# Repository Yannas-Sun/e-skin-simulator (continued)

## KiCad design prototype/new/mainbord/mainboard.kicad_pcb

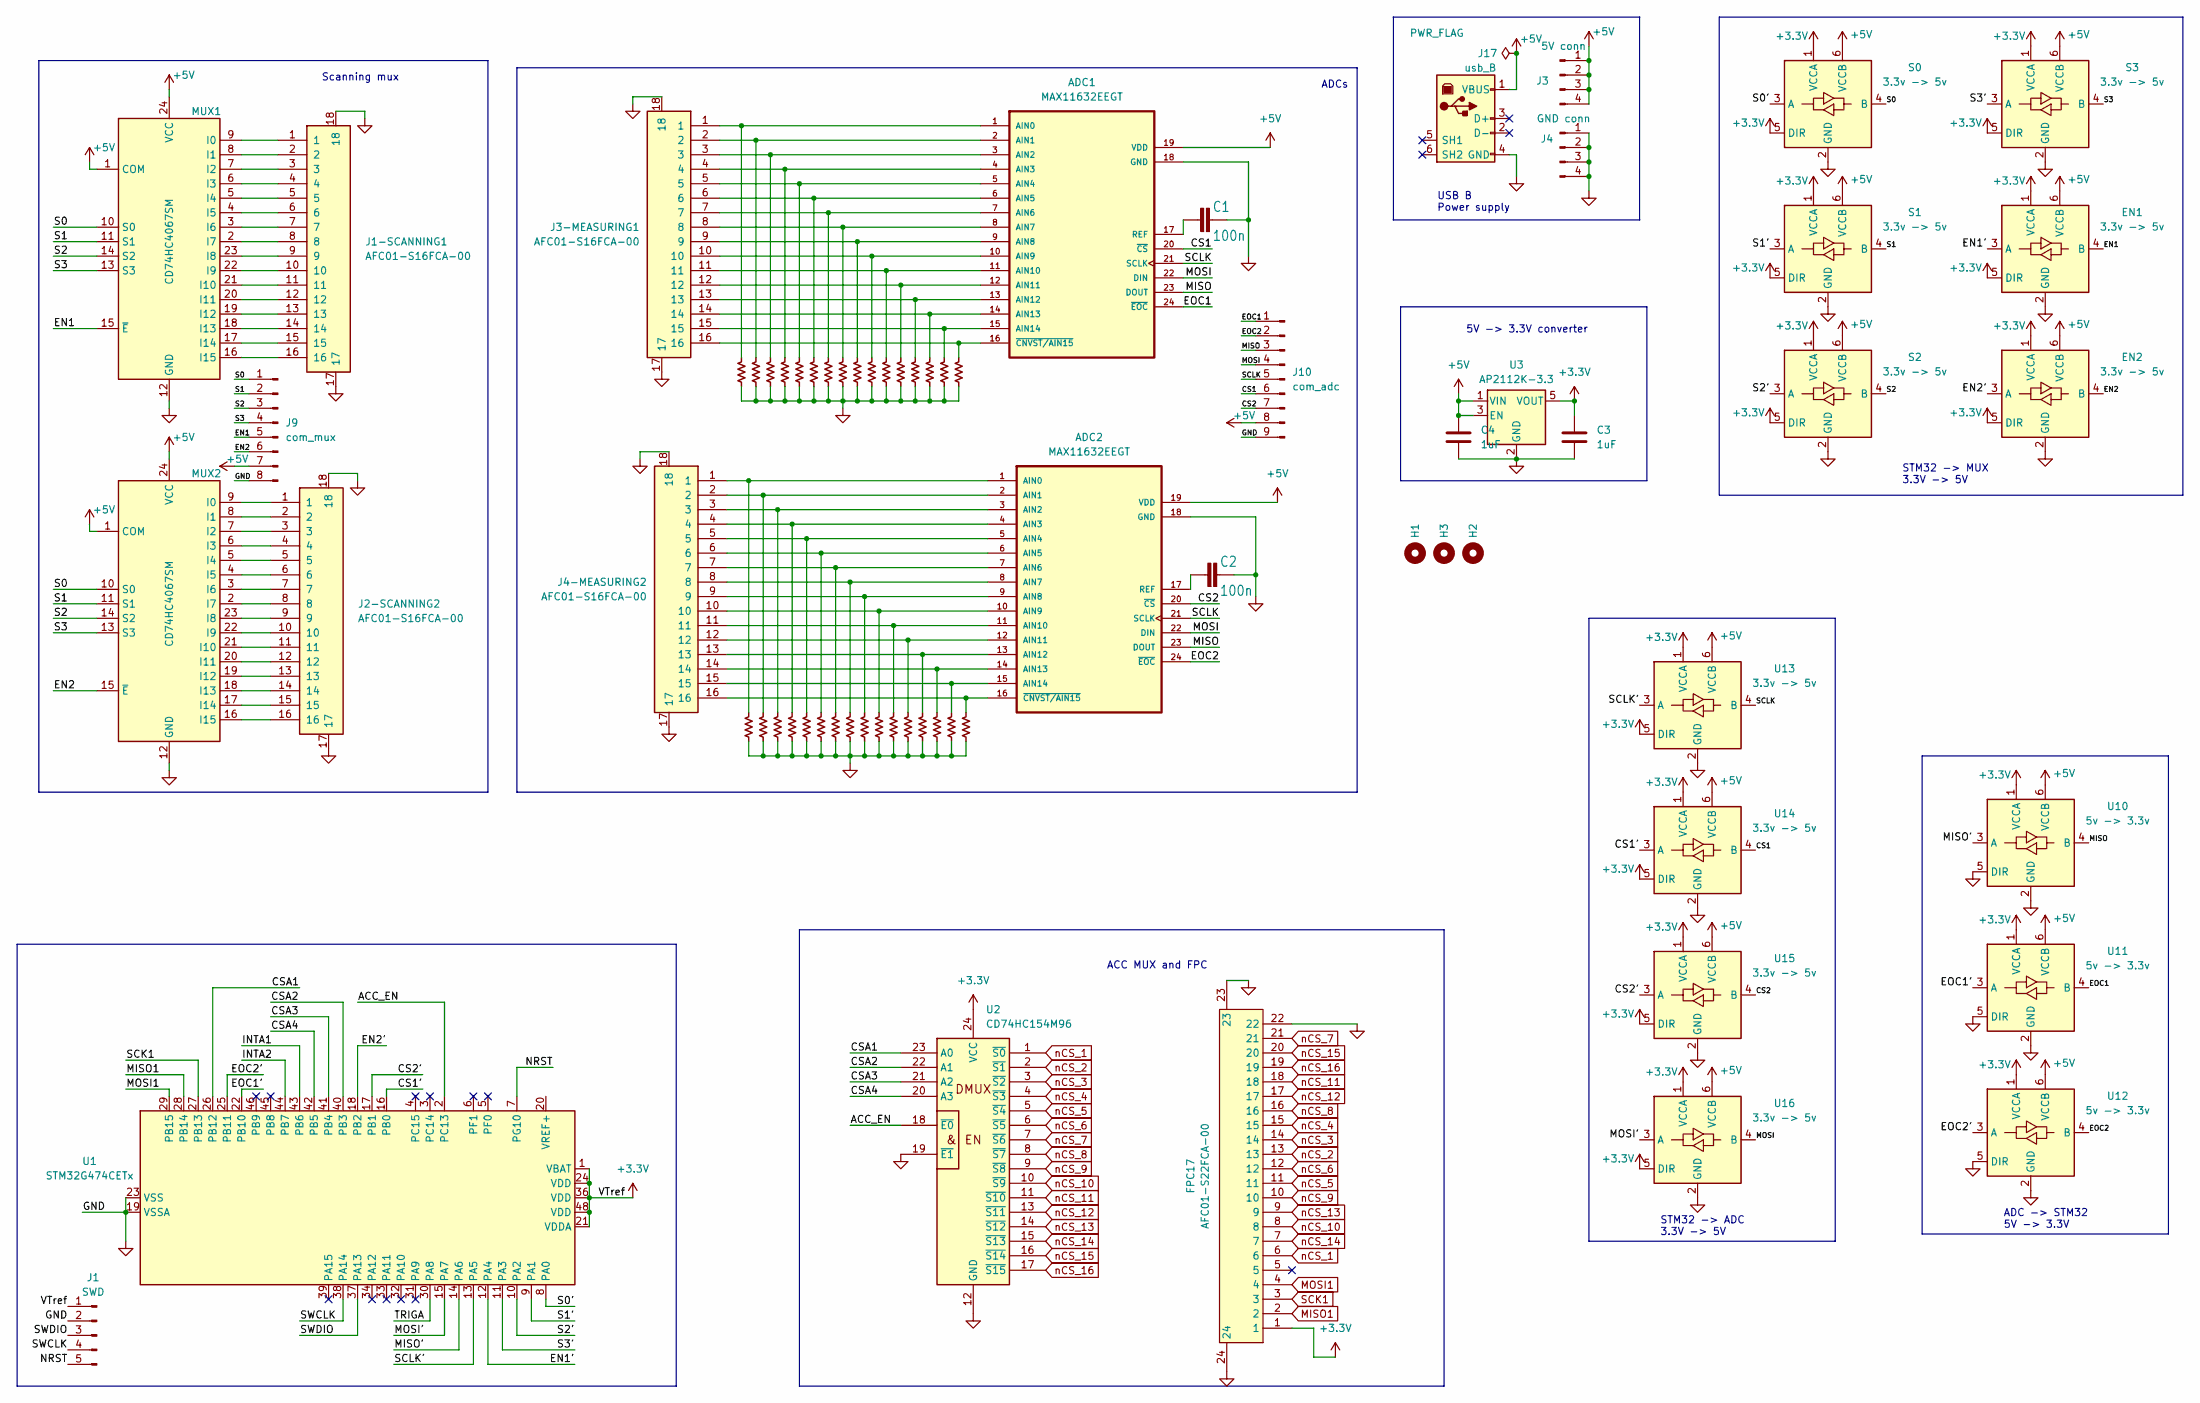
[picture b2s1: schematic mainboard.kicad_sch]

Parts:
ADC1, ADC2: MAX11632EEGT
C1, C2: 100n; C0603
C3, C4: 1uF; C0603
EN1, EN2: 3.3v -> 5v; SOT-363_SC-70-6
FPC17: AFC01-S22FCA-00; LCSC Part C262668
H1, H2, H3: MountingHole; MountingHole_3.2mm_M3
J1: SWD; PinHeader_1x05_P2.54mm_Vertical
J1-SCANNING1, J2-SCANNING2, J3-MEASURING1, J4-MEASURING2: AFC01-S16FCA-00
J3: 5V conn; PinHeader_1x04_P2.54mm_Horizontal
J4: GND conn; PinHeader_1x04_P2.54mm_Horizontal
J9: com_mux; PinHeader_1x08_P2.54mm_Vertical
J10: com_adc; PinHeader_1x09_P2.54mm_Vertical
J17: usb_B; SS52300001; Mouser Part Number 530-SS-52300-001
MUX1, MUX2: CD74HC4067SM; SSOP-24_5.3x8.2mm_P0.65mm
S0, S1, S2, S3: 3.3v -> 5v; SOT-363_SC-70-6
U1: STM32G474CETx; LQFP-48_7x7mm_P0.5mm
U2: CD74HC154M96; SOIC127P1030X265-24N
U3: AP2112K-3.3; SOT-23-5
U10, U11, U12: 5v -> 3.3v; SOT-363_SC-70-6
U13, U14, U15, U16: 3.3v -> 5v; SOT-363_SC-70-6
U$2, U$4, U$6, U$8, U$10, U$12, U$14, U$16, U$18, U$20, U$22, U$24, U$26, U$28, U$30, U$32, U$34, U$36, U$38, U$40, U$42, U$44, U$46, U$48, U$50, U$52, U$54, U$56, U$58, U$60, U$62, U$64: 10k; R_0603_1608Metric

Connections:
+3.3V: C3.1, EN1.1 (VCCA), EN1.5 (DIR), EN2.1 (VCCA), EN2.5 (DIR), FPC17.1, J1.1, S0.1 (VCCA), S0.5 (DIR), S1.1 (VCCA), S1.5 (DIR), S2.1 (VCCA), S2.5 (DIR), S3.1 (VCCA), S3.5 (DIR), U1.1 (VBAT), U1.21 (VDDA), U1.24 (VDD), U1.36 (VDD), U1.48 (VDD), U2.24 (VCC), U3.5 (VOUT), U10.1 (VCCA), U11.1 (VCCA), U12.1 (VCCA), U13.1 (VCCA), U13.5 (DIR), U14.1 (VCCA), U14.5 (DIR), U15.1 (VCCA), U15.5 (DIR), U16.1 (VCCA), U16.5 (DIR)
+5V: ADC1.19 (VDD), ADC2.19 (VDD), C4.1, EN1.6 (VCCB), EN2.6 (VCCB), J3.1, J3.2, J3.3, J3.4, J9.7, J10.8, J17.1 (VBUS), MUX1.1 (COM), MUX1.24 (VCC), MUX2.1 (COM), MUX2.24 (VCC), S0.6 (VCCB), S1.6 (VCCB), S2.6 (VCCB), S3.6 (VCCB), U3.1 (VIN), U3.3 (EN), U10.6 (VCCB), U11.6 (VCCB), U12.6 (VCCB), U13.6 (VCCB), U14.6 (VCCB), U15.6 (VCCB), U16.6 (VCCB)
/ACC_EN: U1.2 (PC13), U2.18 (~E0)
/CS1: ADC1.20 (~CS), J10.6, U14.4 (B)
/CS1': U1.16 (PB0), U14.3 (A)
/CS2: ADC2.20 (~CS), J10.7, U15.4 (B)
/CS2': U1.17 (PB1), U15.3 (A)
/CSA1: U1.26 (PB12), U2.23 (A0)
/CSA2: U1.40 (PB3), U2.22 (A1)
/CSA3: U1.41 (PB4), U2.21 (A2)
/CSA4: U1.42 (PB5), U2.20 (A3)
/EN1: EN1.4 (B), J9.5, MUX1.15 (~E)
/EN1': EN1.3 (A), U1.12 (PA4)
/EN2: EN2.4 (B), J9.6, MUX2.15 (~E)
/EN2': EN2.3 (A), U1.18 (PB2)
/EOC1: ADC1.24 (~EOC), J10.1, U11.4 (B)
/EOC1': U1.22 (PB10), U11.3 (A)
/EOC2: ADC2.24 (~EOC), J10.2, U12.4 (B)
/EOC2': U1.25 (PB11), U12.3 (A)
/INTA1: U1.43 (PB6)
/INTA2: U1.44 (PB7)
/MISO: ADC1.23 (DOUT), ADC2.23 (DOUT), J10.3, U10.4 (B)
/MISO': U1.14 (PA6), U10.3 (A)
/MOSI: ADC1.22 (DIN), ADC2.22 (DIN), J10.4, U16.4 (B)
/MOSI': U1.15 (PA7), U16.3 (A)
/NRST: J1.5, U1.7 (PG10)
/S0: J9.1, MUX1.10 (S0), MUX2.10 (S0), S0.4 (B)
/S0': S0.3 (A), U1.8 (PA0)
/S1: J9.2, MUX1.11 (S1), MUX2.11 (S1), S1.4 (B)
/S1': S1.3 (A), U1.9 (PA1)
/S2: J9.3, MUX1.14 (S2), MUX2.14 (S2), S2.4 (B)
/S2': S2.3 (A), U1.10 (PA2)
/S3: J9.4, MUX1.13 (S3), MUX2.13 (S3), S3.4 (B)
/S3': S3.3 (A), U1.11 (PA3)
/SCLK: ADC1.21 (SCLK), ADC2.21 (SCLK), J10.5, U13.4 (B)
/SCLK': U1.13 (PA5), U13.3 (A)
/SWCLK: J1.4, U1.38 (PA14)
/SWDIO: J1.3, U1.37 (PA13)
/TRIGA: U1.30 (PA8)
GND: ADC1.18 (GND), ADC2.18 (GND), C1.2, C2.2, C3.2, C4.2, EN1.2 (GND), EN2.2 (GND), FPC17.22, FPC17.23, FPC17.24, J1.2, J1-SCANNING1.17, J1-SCANNING1.18, J2-SCANNING2.17, J2-SCANNING2.18, J3-MEASURING1.17, J3-MEASURING1.18, J4.1, J4.2, J4.3, J4.4, J4-MEASURING2.17, J4-MEASURING2.18, J9.8, J10.9, J17.4 (GND), MUX1.12 (GND), MUX2.12 (GND), S0.2 (GND), S1.2 (GND), S2.2 (GND), S3.2 (GND), U1.19 (VSSA), U1.23 (VSS), U1.35 (VSS), U1.47 (VSS), U2.12 (GND), U2.19 (~E1), U3.2 (GND), U10.2 (GND), U10.5 (DIR), U11.2 (GND), U11.5 (DIR), U12.2 (GND), U12.5 (DIR), U13.2 (GND), U14.2 (GND), U15.2 (GND), U16.2 (GND), U$2.2, U$4.2, U$6.2, U$8.2, U$10.2, U$12.2, U$14.2, U$16.2, U$18.2, U$20.2, U$22.2, U$24.2, U$26.2, U$28.2, U$30.2, U$32.2, U$34.2, U$36.2, U$38.2, U$40.2, U$42.2, U$44.2, U$46.2, U$48.2, U$50.2, U$52.2, U$54.2, U$56.2, U$58.2, U$60.2, U$62.2, U$64.2
MISO1: FPC17.2, U1.28 (PB14)
MOSI1: FPC17.4, U1.29 (PB15)
unnamed: ADC1.1 (AIN0), J3-MEASURING1.1, U$16.1
unnamed: ADC1.2 (AIN1), J3-MEASURING1.2, U$14.1
unnamed: ADC1.3 (AIN2), J3-MEASURING1.3, U$12.1
unnamed: ADC1.4 (AIN3), J3-MEASURING1.4, U$10.1
unnamed: ADC1.5 (AIN4), J3-MEASURING1.5, U$8.1
unnamed: ADC1.6 (AIN5), J3-MEASURING1.6, U$6.1
unnamed: ADC1.7 (AIN6), J3-MEASURING1.7, U$4.1
unnamed: ADC1.8 (AIN7), J3-MEASURING1.8, U$2.1
unnamed: ADC1.9 (AIN8), J3-MEASURING1.9, U$32.1
unnamed: ADC1.10 (AIN9), J3-MEASURING1.10, U$30.1
unnamed: ADC1.11 (AIN10), J3-MEASURING1.11, U$28.1
unnamed: ADC1.12 (AIN11), J3-MEASURING1.12, U$26.1
unnamed: ADC1.13 (AIN12), J3-MEASURING1.13, U$24.1
unnamed: ADC1.14 (AIN13), J3-MEASURING1.14, U$22.1
unnamed: ADC1.15 (AIN14), J3-MEASURING1.15, U$20.1
unnamed: ADC1.17 (REF), C1.1
unnamed: ADC1.16 (~CNVST/AIN15), J3-MEASURING1.16, U$18.1
unnamed: ADC2.1 (AIN0), J4-MEASURING2.1, U$48.1
unnamed: ADC2.2 (AIN1), J4-MEASURING2.2, U$46.1
unnamed: ADC2.3 (AIN2), J4-MEASURING2.3, U$44.1
unnamed: ADC2.4 (AIN3), J4-MEASURING2.4, U$42.1
unnamed: ADC2.5 (AIN4), J4-MEASURING2.5, U$40.1
unnamed: ADC2.6 (AIN5), J4-MEASURING2.6, U$38.1
unnamed: ADC2.7 (AIN6), J4-MEASURING2.7, U$36.1
unnamed: ADC2.8 (AIN7), J4-MEASURING2.8, U$34.1
unnamed: ADC2.9 (AIN8), J4-MEASURING2.9, U$64.1
unnamed: ADC2.10 (AIN9), J4-MEASURING2.10, U$62.1
unnamed: ADC2.11 (AIN10), J4-MEASURING2.11, U$60.1
unnamed: ADC2.12 (AIN11), J4-MEASURING2.12, U$58.1
unnamed: ADC2.13 (AIN12), J4-MEASURING2.13, U$56.1
unnamed: ADC2.14 (AIN13), J4-MEASURING2.14, U$54.1
unnamed: ADC2.15 (AIN14), J4-MEASURING2.15, U$52.1
unnamed: ADC2.17 (REF), C2.1
unnamed: ADC2.16 (~CNVST/AIN15), J4-MEASURING2.16, U$50.1
unnamed: J1-SCANNING1.1, MUX1.9 (I0)
unnamed: J1-SCANNING1.2, MUX1.8 (I1)
unnamed: J1-SCANNING1.3, MUX1.7 (I2)
unnamed: J1-SCANNING1.4, MUX1.6 (I3)
unnamed: J1-SCANNING1.5, MUX1.5 (I4)
unnamed: J1-SCANNING1.6, MUX1.4 (I5)
unnamed: J1-SCANNING1.7, MUX1.3 (I6)
unnamed: J1-SCANNING1.8, MUX1.2 (I7)
unnamed: J1-SCANNING1.9, MUX1.23 (I8)
unnamed: J1-SCANNING1.10, MUX1.22 (I9)
unnamed: J1-SCANNING1.11, MUX1.21 (I10)
unnamed: J1-SCANNING1.12, MUX1.20 (I11)
unnamed: J1-SCANNING1.13, MUX1.19 (I12)
unnamed: J1-SCANNING1.14, MUX1.18 (I13)
unnamed: J1-SCANNING1.15, MUX1.17 (I14)
unnamed: J1-SCANNING1.16, MUX1.16 (I15)
unnamed: J2-SCANNING2.1, MUX2.9 (I0)
unnamed: J2-SCANNING2.2, MUX2.8 (I1)
unnamed: J2-SCANNING2.3, MUX2.7 (I2)
unnamed: J2-SCANNING2.4, MUX2.6 (I3)
unnamed: J2-SCANNING2.5, MUX2.5 (I4)
unnamed: J2-SCANNING2.6, MUX2.4 (I5)
unnamed: J2-SCANNING2.7, MUX2.3 (I6)
unnamed: J2-SCANNING2.8, MUX2.2 (I7)
unnamed: J2-SCANNING2.9, MUX2.23 (I8)
unnamed: J2-SCANNING2.10, MUX2.22 (I9)
unnamed: J2-SCANNING2.11, MUX2.21 (I10)
unnamed: J2-SCANNING2.12, MUX2.20 (I11)
unnamed: J2-SCANNING2.13, MUX2.19 (I12)
unnamed: J2-SCANNING2.14, MUX2.18 (I13)
unnamed: J2-SCANNING2.15, MUX2.17 (I14)
unnamed: J2-SCANNING2.16, MUX2.16 (I15)
SCK1: FPC17.3, U1.27 (PB13)
nCS_1: FPC17.6, U2.1 (~S0)
nCS_2: FPC17.13, U2.2 (~S1)
nCS_3: FPC17.14, U2.3 (~S2)
nCS_4: FPC17.15, U2.4 (~S3)
nCS_5: FPC17.11, U2.5 (~S4)
nCS_6: FPC17.12, U2.6 (~S5)
nCS_7: FPC17.21, U2.7 (~S6)
nCS_8: FPC17.16, U2.8 (~S7)
nCS_9: FPC17.10, U2.9 (~S8)
nCS_10: FPC17.8, U2.10 (~S9)
nCS_11: FPC17.18, U2.11 (~S10)
nCS_12: FPC17.17, U2.13 (~S11)
nCS_13: FPC17.9, U2.14 (~S12)
nCS_14: FPC17.7, U2.15 (~S13)
nCS_15: FPC17.20, U2.16 (~S14)
nCS_16: FPC17.19, U2.17 (~S15)

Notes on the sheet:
ADCs
USB B Power supply
ADC -> STM32 5V -> 3.3V
STM32 -> MUX 3.3V -> 5V
5V -> 3.3V converter
ACC MUX and FPC
Scanning mux
STM32 -> ADC 3.3V -> 5V

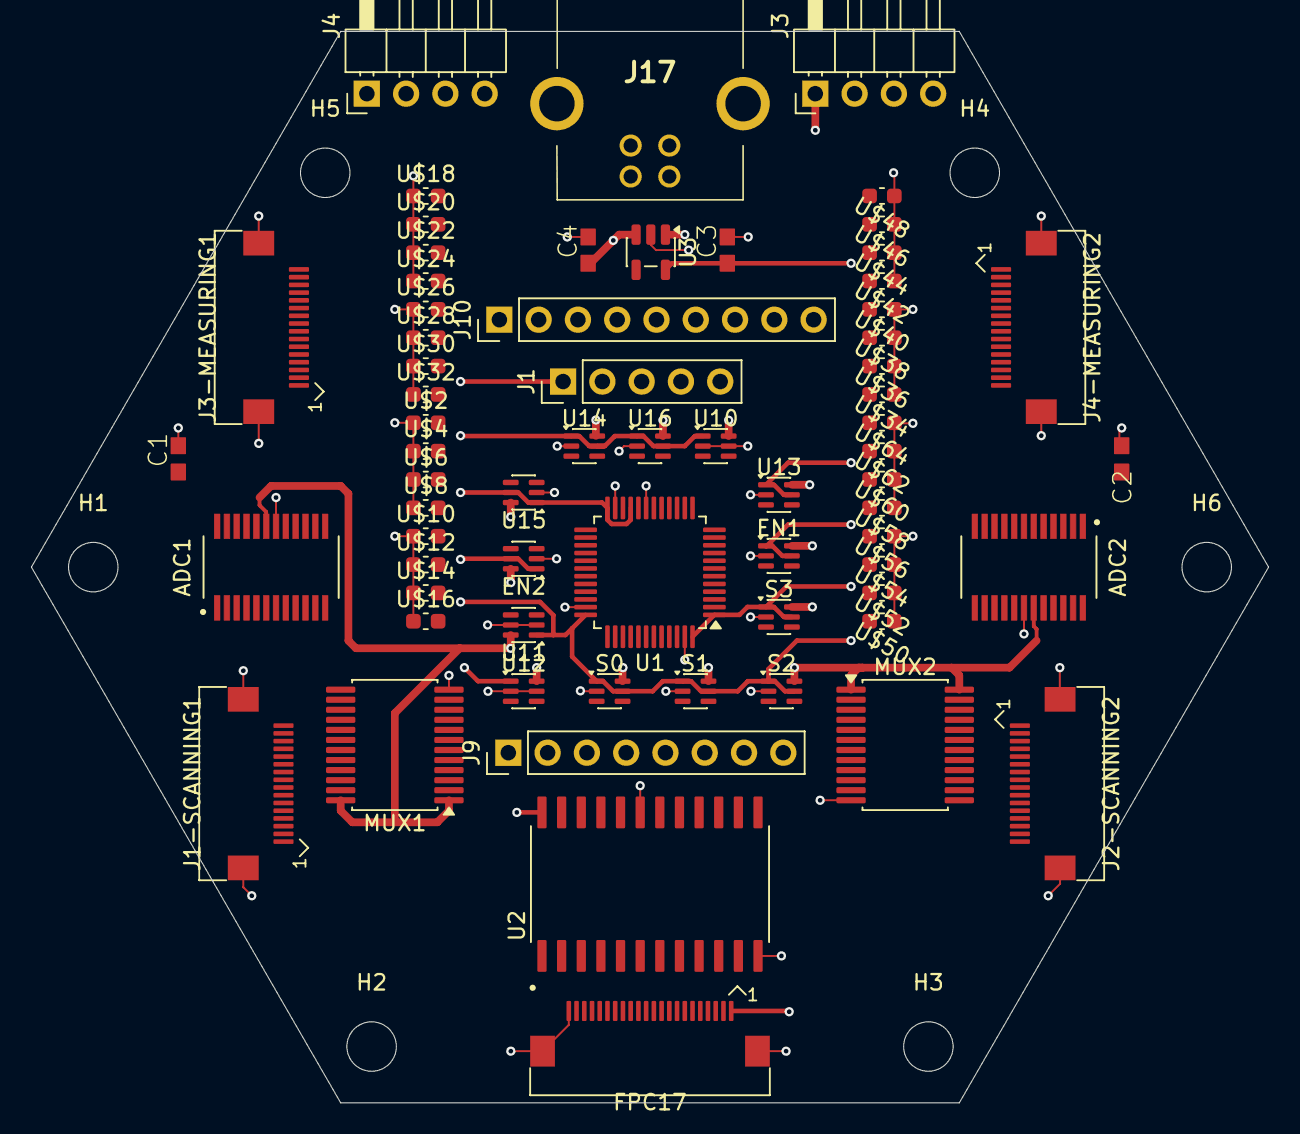
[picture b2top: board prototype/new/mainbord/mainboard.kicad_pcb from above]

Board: 4 copper layers, 80.0 x 69.3 mm, 73 parts (0 on the bottom side), 122 nets.

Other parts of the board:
H4, H5, H6: MountingHole; MountingHole_3.2mm_M3

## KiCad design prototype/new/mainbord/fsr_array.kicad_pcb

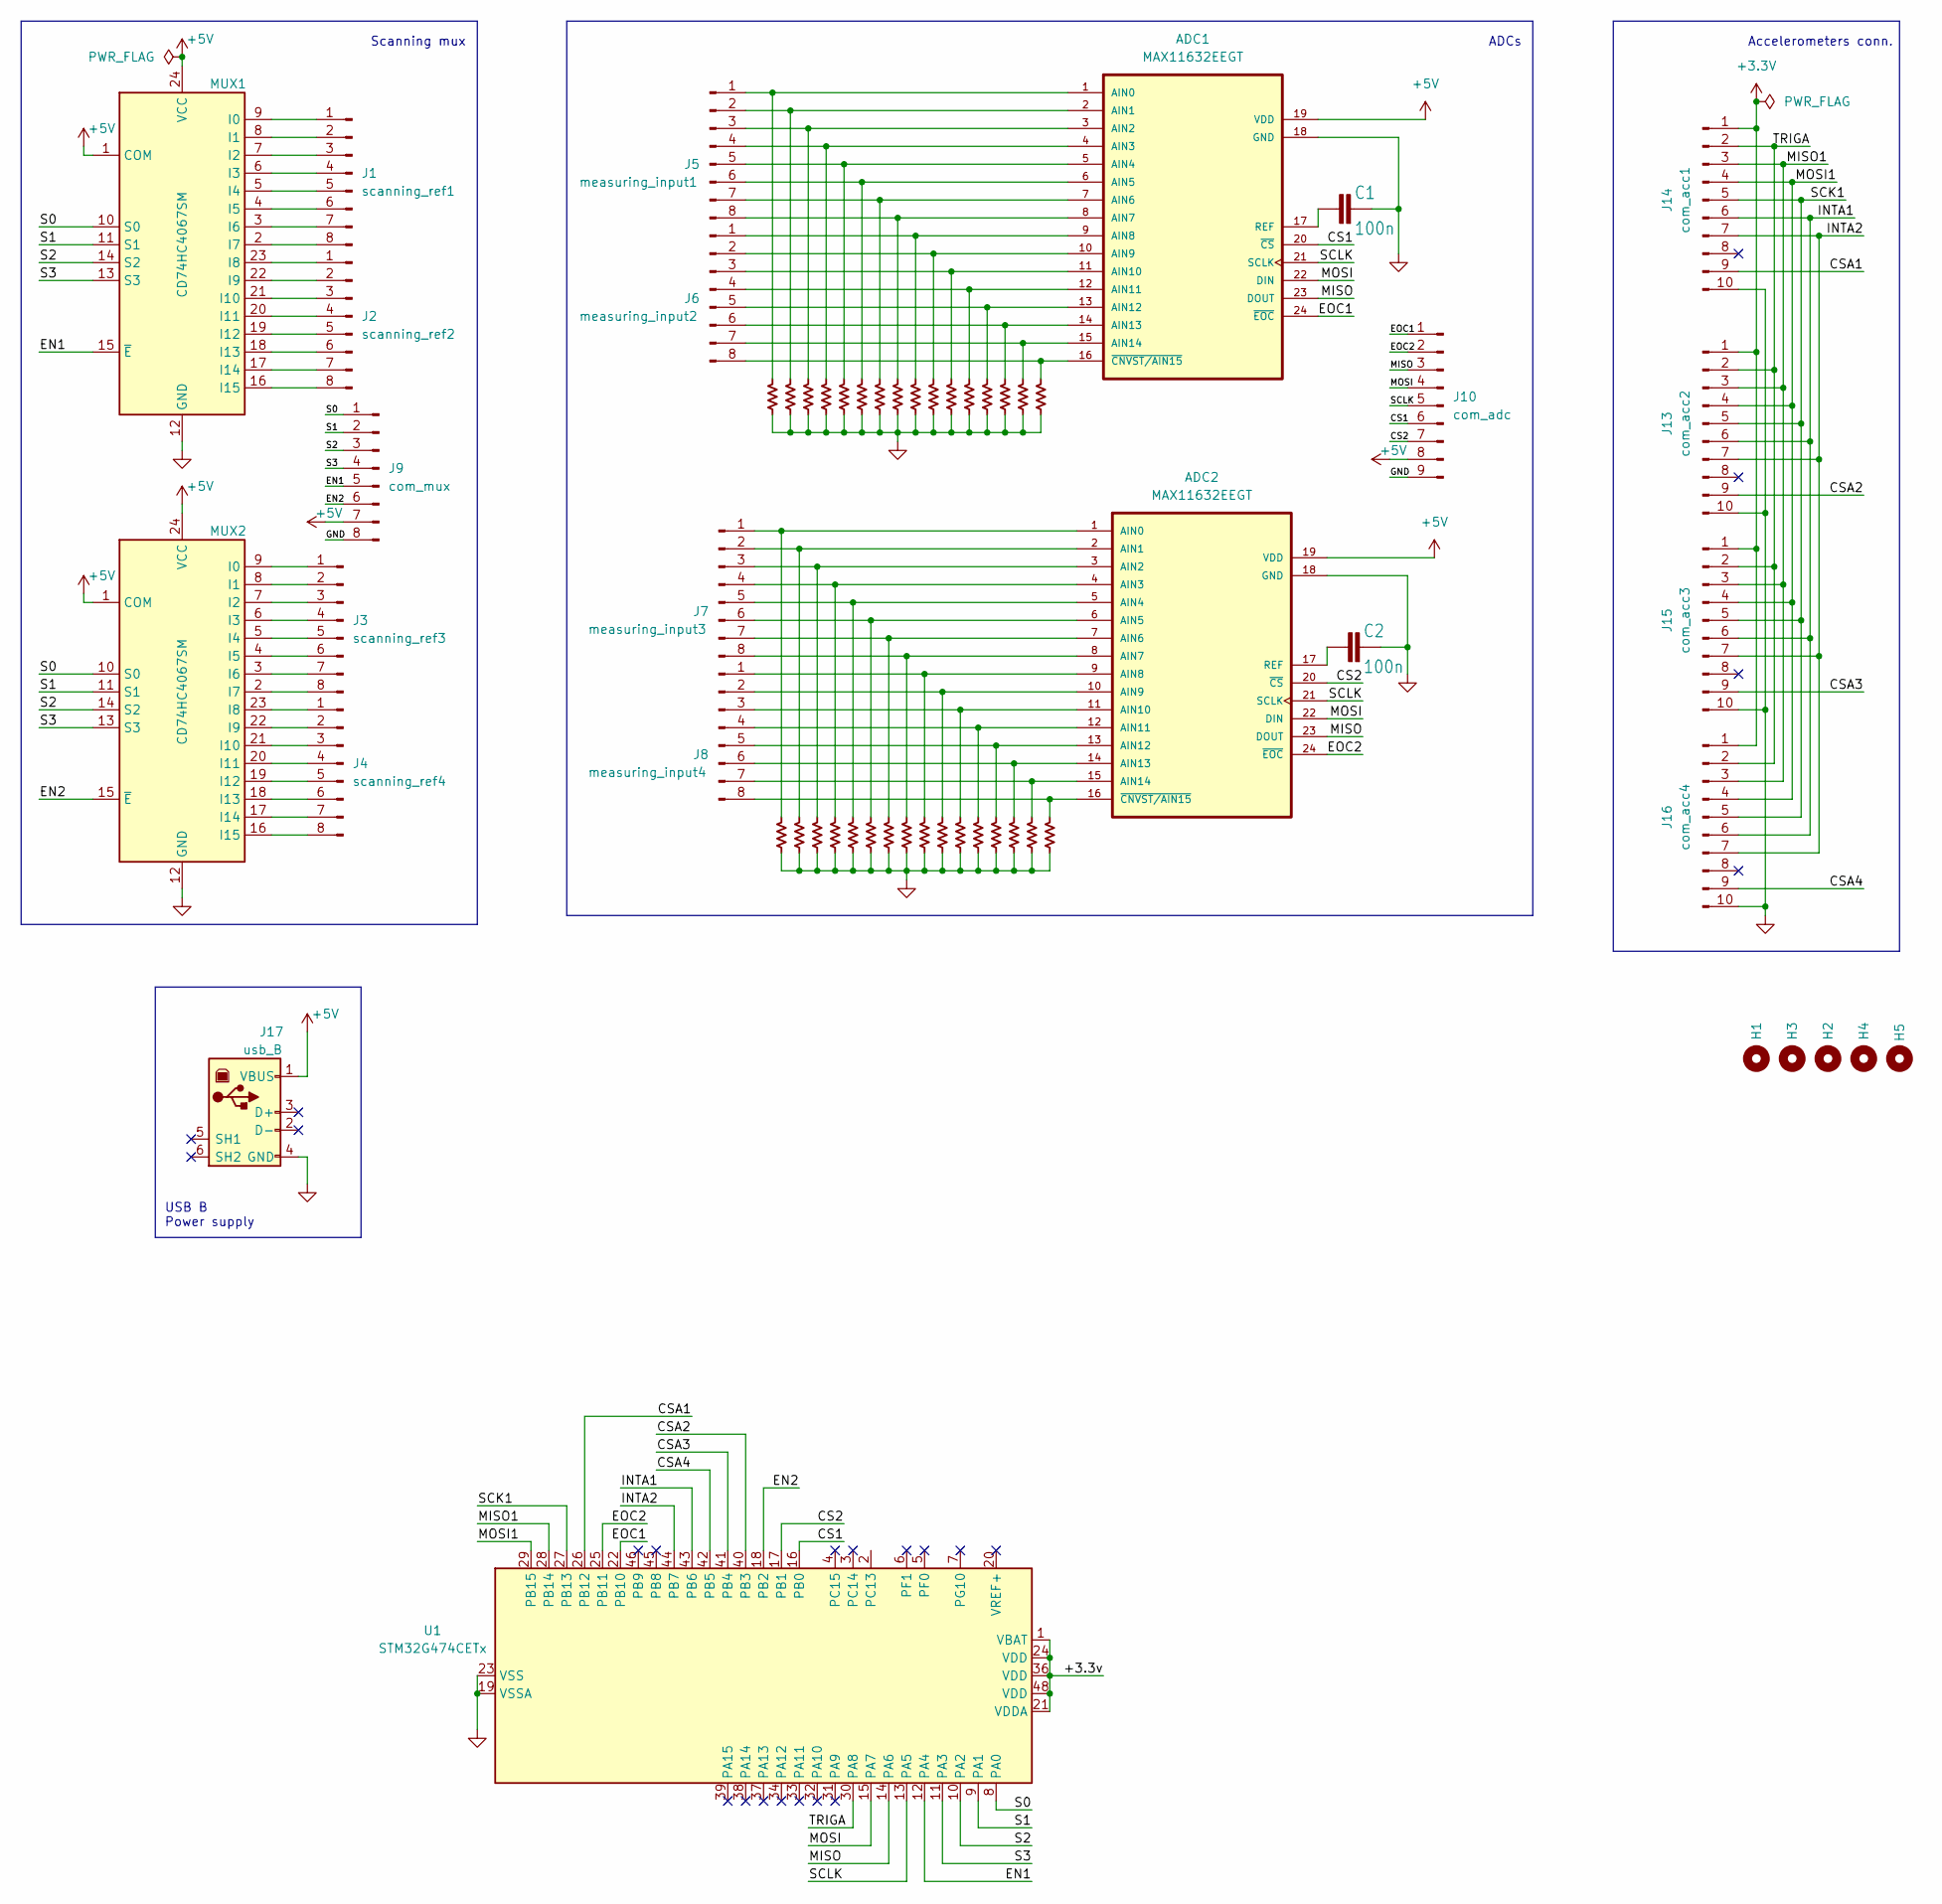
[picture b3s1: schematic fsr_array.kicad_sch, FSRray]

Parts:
ADC1, ADC2: MAX11632EEGT
C1, C2: 100n; C0603
H1, H2, H3, H4, H5: MountingHole; MountingHole_3.2mm_M3
J1: scanning_ref1; PinHeader_1x08_P2.54mm_Vertical
J2: scanning_ref2; PinHeader_1x08_P2.54mm_Vertical
J3: scanning_ref3; PinHeader_1x08_P2.54mm_Vertical
J4: scanning_ref4; PinHeader_1x08_P2.54mm_Vertical
J5: measuring_input1; PinHeader_1x08_P2.54mm_Vertical
J6: measuring_input2; PinHeader_1x08_P2.54mm_Vertical
J7: measuring_input3; PinHeader_1x08_P2.54mm_Vertical
J8: measuring_input4; PinHeader_1x08_P2.54mm_Vertical
J9: com_mux; PinHeader_1x08_P2.54mm_Vertical
J10: com_adc; PinHeader_1x09_P2.54mm_Vertical
J13: com_acc2; PinHeader_2x05_P1.27mm_Vertical
J14: com_acc1; PinHeader_2x05_P1.27mm_Vertical
J15: com_acc3; PinHeader_2x05_P1.27mm_Vertical
J16: com_acc4; PinHeader_2x05_P1.27mm_Vertical
J17: usb_B; SS52300001; Mouser Part Number 530-SS-52300-001
MUX1, MUX2: CD74HC4067SM; SSOP-24_5.3x8.2mm_P0.65mm
U1: STM32G474CETx; LQFP-48_7x7mm_P0.5mm
U$2, U$4, U$6, U$8, U$10, U$12, U$14, U$16, U$18, U$20, U$22, U$24, U$26, U$28, U$30, U$32, U$34, U$36, U$38, U$40, U$42, U$44, U$46, U$48, U$50, U$52, U$54, U$56, U$58, U$60, U$62, U$64: 10k; R_0603_1608Metric

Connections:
+3.3V: J13.1, J14.1, J15.1, J16.1
+5V: ADC1.19 (VDD), ADC2.19 (VDD), J9.7, J10.8, J17.1 (VBUS), MUX1.1 (COM), MUX1.24 (VCC), MUX2.1 (COM), MUX2.24 (VCC)
/+3.3v: U1.1 (VBAT), U1.21 (VDDA), U1.24 (VDD), U1.36 (VDD), U1.48 (VDD)
/CS1: ADC1.20 (~CS), J10.6, U1.16 (PB0)
/CS2: ADC2.20 (~CS), J10.7, U1.17 (PB1)
/CSA1: J14.9, U1.26 (PB12)
/CSA2: J13.9, U1.40 (PB3)
/CSA3: J15.9, U1.41 (PB4)
/CSA4: J16.9, U1.42 (PB5)
/EN1: J9.5, MUX1.15 (~E), U1.12 (PA4)
/EN2: J9.6, MUX2.15 (~E), U1.18 (PB2)
/EOC1: ADC1.24 (~EOC), J10.1, U1.22 (PB10)
/EOC2: ADC2.24 (~EOC), J10.2, U1.25 (PB11)
/INTA1: J13.6, J14.6, J15.6, J16.6, U1.43 (PB6)
/INTA2: J13.7, J14.7, J15.7, J16.7, U1.44 (PB7)
/MISO: ADC1.23 (DOUT), ADC2.23 (DOUT), J10.3, U1.14 (PA6)
/MISO1: J13.3, J14.3, J15.3, J16.3, U1.28 (PB14)
/MOSI: ADC1.22 (DIN), ADC2.22 (DIN), J10.4, U1.15 (PA7)
/MOSI1: J13.4, J14.4, J15.4, J16.4, U1.29 (PB15)
/S0: J9.1, MUX1.10 (S0), MUX2.10 (S0), U1.8 (PA0)
/S1: J9.2, MUX1.11 (S1), MUX2.11 (S1), U1.9 (PA1)
/S2: J9.3, MUX1.14 (S2), MUX2.14 (S2), U1.10 (PA2)
/S3: J9.4, MUX1.13 (S3), MUX2.13 (S3), U1.11 (PA3)
/SCK1: J13.5, J14.5, J15.5, J16.5, U1.27 (PB13)
/SCLK: ADC1.21 (SCLK), ADC2.21 (SCLK), J10.5, U1.13 (PA5)
/TRIGA: J13.2, J14.2, J15.2, J16.2, U1.30 (PA8)
GND: ADC1.18 (GND), ADC2.18 (GND), C1.2, C2.2, J9.8, J10.9, J13.10, J14.10, J15.10, J16.10, J17.4 (GND), MUX1.12 (GND), MUX2.12 (GND), U1.19 (VSSA), U1.23 (VSS), U1.35 (VSS), U1.47 (VSS), U$2.2, U$4.2, U$6.2, U$8.2, U$10.2, U$12.2, U$14.2, U$16.2, U$18.2, U$20.2, U$22.2, U$24.2, U$26.2, U$28.2, U$30.2, U$32.2, U$34.2, U$36.2, U$38.2, U$40.2, U$42.2, U$44.2, U$46.2, U$48.2, U$50.2, U$52.2, U$54.2, U$56.2, U$58.2, U$60.2, U$62.2, U$64.2
unnamed: ADC1.1 (AIN0), J5.1, U$16.1
unnamed: ADC1.2 (AIN1), J5.2, U$14.1
unnamed: ADC1.3 (AIN2), J5.3, U$12.1
unnamed: ADC1.4 (AIN3), J5.4, U$10.1
unnamed: ADC1.5 (AIN4), J5.5, U$8.1
unnamed: ADC1.6 (AIN5), J5.6, U$6.1
unnamed: ADC1.7 (AIN6), J5.7, U$4.1
unnamed: ADC1.8 (AIN7), J5.8, U$2.1
unnamed: ADC1.9 (AIN8), J6.1, U$32.1
unnamed: ADC1.10 (AIN9), J6.2, U$30.1
unnamed: ADC1.11 (AIN10), J6.3, U$28.1
unnamed: ADC1.12 (AIN11), J6.4, U$26.1
unnamed: ADC1.13 (AIN12), J6.5, U$24.1
unnamed: ADC1.14 (AIN13), J6.6, U$22.1
unnamed: ADC1.15 (AIN14), J6.7, U$20.1
unnamed: ADC1.17 (REF), C1.1
unnamed: ADC1.16 (~CNVST/AIN15), J6.8, U$18.1
unnamed: ADC2.1 (AIN0), J7.1, U$48.1
unnamed: ADC2.2 (AIN1), J7.2, U$46.1
unnamed: ADC2.3 (AIN2), J7.3, U$44.1
unnamed: ADC2.4 (AIN3), J7.4, U$42.1
unnamed: ADC2.5 (AIN4), J7.5, U$40.1
unnamed: ADC2.6 (AIN5), J7.6, U$38.1
unnamed: ADC2.7 (AIN6), J7.7, U$36.1
unnamed: ADC2.8 (AIN7), J7.8, U$34.1
unnamed: ADC2.9 (AIN8), J8.1, U$64.1
unnamed: ADC2.10 (AIN9), J8.2, U$62.1
unnamed: ADC2.11 (AIN10), J8.3, U$60.1
unnamed: ADC2.12 (AIN11), J8.4, U$58.1
unnamed: ADC2.13 (AIN12), J8.5, U$56.1
unnamed: ADC2.14 (AIN13), J8.6, U$54.1
unnamed: ADC2.15 (AIN14), J8.7, U$52.1
unnamed: ADC2.17 (REF), C2.1
unnamed: ADC2.16 (~CNVST/AIN15), J8.8, U$50.1
unnamed: J1.1, MUX1.9 (I0)
unnamed: J1.2, MUX1.8 (I1)
unnamed: J1.3, MUX1.7 (I2)
unnamed: J1.4, MUX1.6 (I3)
unnamed: J1.5, MUX1.5 (I4)
unnamed: J1.6, MUX1.4 (I5)
unnamed: J1.7, MUX1.3 (I6)
unnamed: J1.8, MUX1.2 (I7)
unnamed: J2.1, MUX1.23 (I8)
unnamed: J2.2, MUX1.22 (I9)
unnamed: J2.3, MUX1.21 (I10)
unnamed: J2.4, MUX1.20 (I11)
unnamed: J2.5, MUX1.19 (I12)
unnamed: J2.6, MUX1.18 (I13)
unnamed: J2.7, MUX1.17 (I14)
unnamed: J2.8, MUX1.16 (I15)
unnamed: J3.1, MUX2.9 (I0)
unnamed: J3.2, MUX2.8 (I1)
unnamed: J3.3, MUX2.7 (I2)
unnamed: J3.4, MUX2.6 (I3)
unnamed: J3.5, MUX2.5 (I4)
unnamed: J3.6, MUX2.4 (I5)
unnamed: J3.7, MUX2.3 (I6)
unnamed: J3.8, MUX2.2 (I7)
unnamed: J4.1, MUX2.23 (I8)
unnamed: J4.2, MUX2.22 (I9)
unnamed: J4.3, MUX2.21 (I10)
unnamed: J4.4, MUX2.20 (I11)
unnamed: J4.5, MUX2.19 (I12)
unnamed: J4.6, MUX2.18 (I13)
unnamed: J4.7, MUX2.17 (I14)
unnamed: J4.8, MUX2.16 (I15)

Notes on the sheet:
ADCs
USB B Power supply
Accelerometers conn.
Scanning mux

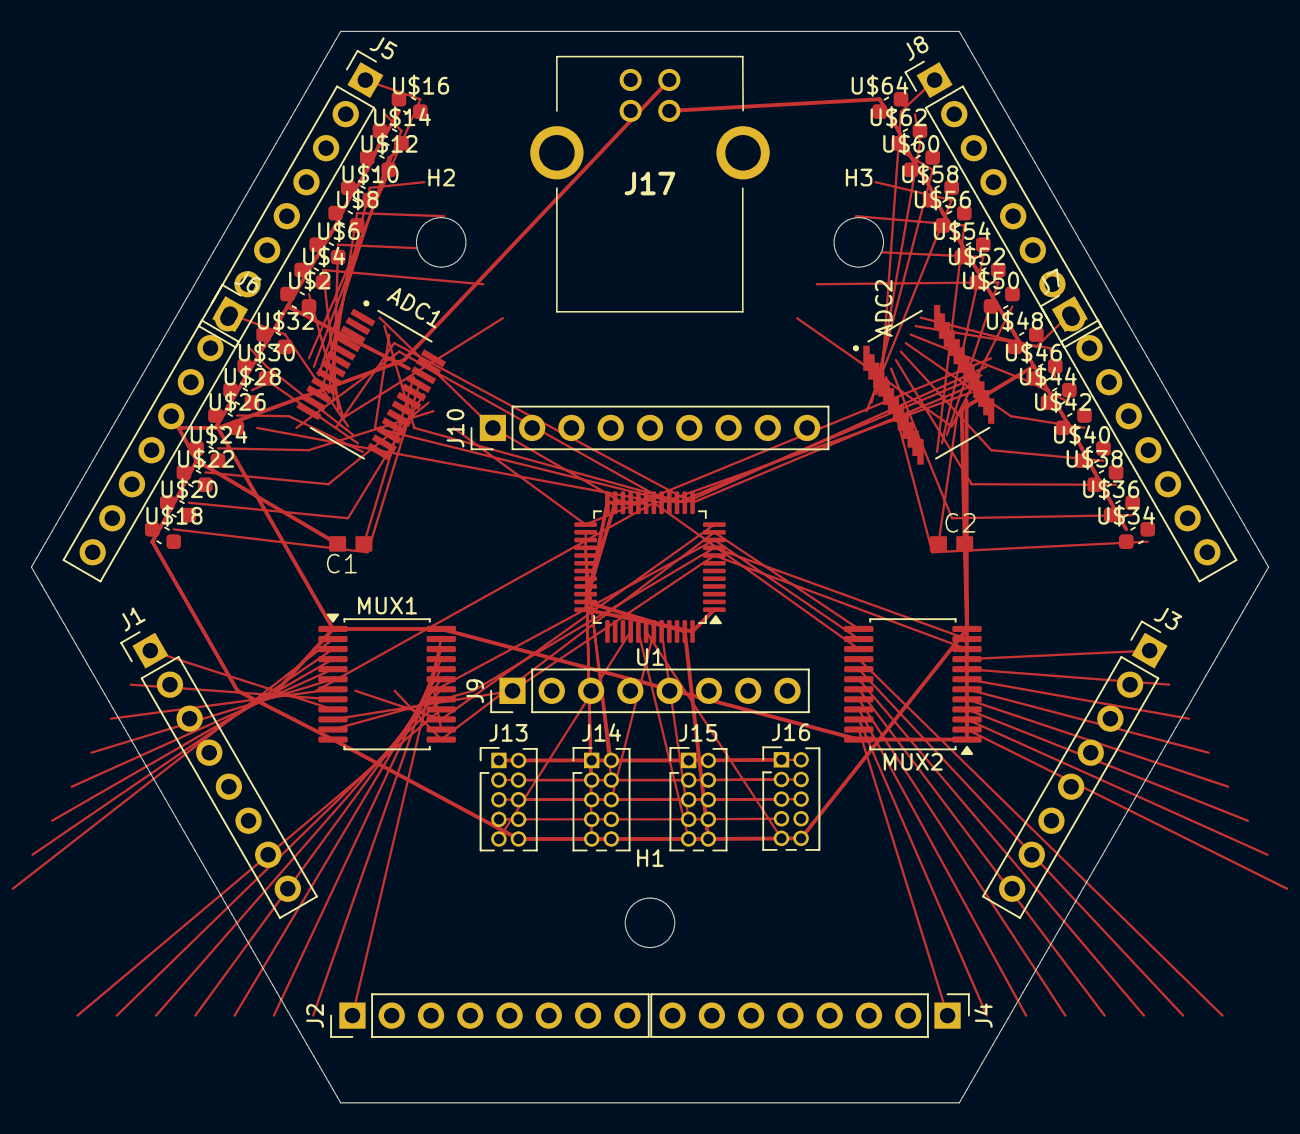
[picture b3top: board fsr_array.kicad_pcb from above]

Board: 4 copper layers, 80.0 x 69.3 mm, 57 parts (0 on the bottom side), 93 nets.

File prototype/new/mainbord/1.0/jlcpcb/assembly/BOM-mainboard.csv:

Comment,Designator,Footprint,LCSC
MAX11632EEGT,ADC1,MAX11632EEGT,
MAX11632EEGT,ADC2,MAX11632EEGT,
usb_B,J17,usbB_stewart,
MountingHole,H5,MountingHole_3.2mm_M3,
100n,C2,C0603,
measuring_input2,J6,PinHeader_1x08_P2.54mm_Vertical,
100n,C1,C0603,
scanning_ref4,J4,PinHeader_1x08_P2.54mm_Vertical,
MountingHole,H1,MountingHole_3.2mm_M3,
teensy_left,J12,PinSocket_1x24_P2.54mm_Vertical,
CD74HC4067SM,MUX2,SSOP-24_5.3x8.2mm_P0.65mm,
com_adc,J10,PinHeader_1x09_P2.54mm_Vertical,
scanning_ref1,J1,PinHeader_1x08_P2.54mm_Vertical,
com_acc1,J14,PinHeader_2x05_P1.27mm_Vertical,
scanning_ref3,J3,PinHeader_1x08_P2.54mm_Vertical,
com_acc2,J13,PinHeader_2x05_P1.27mm_Vertical,
MountingHole,H3,MountingHole_3.2mm_M3,
teensy_right,J11,PinSocket_1x24_P2.54mm_Vertical,
com_mux,J9,PinHeader_1x08_P2.54mm_Vertical,
measuring_input3,J7,PinHeader_1x08_P2.54mm_Vertical,
measuring_input4,J8,PinHeader_1x08_P2.54mm_Vertical,
MountingHole,H4,MountingHole_3.2mm_M3,
MountingHole,H2,MountingHole_3.2mm_M3,
com_acc4,J16,PinHeader_2x05_P1.27mm_Vertical,
com_acc3,J15,PinHeader_2x05_P1.27mm_Vertical,
measuring_input1,J5,PinHeader_1x08_P2.54mm_Vertical,
CD74HC4067SM,MUX1,SSOP-24_5.3x8.2mm_P0.65mm,
scanning_ref2,J2,PinHeader_1x08_P2.54mm_Vertical,

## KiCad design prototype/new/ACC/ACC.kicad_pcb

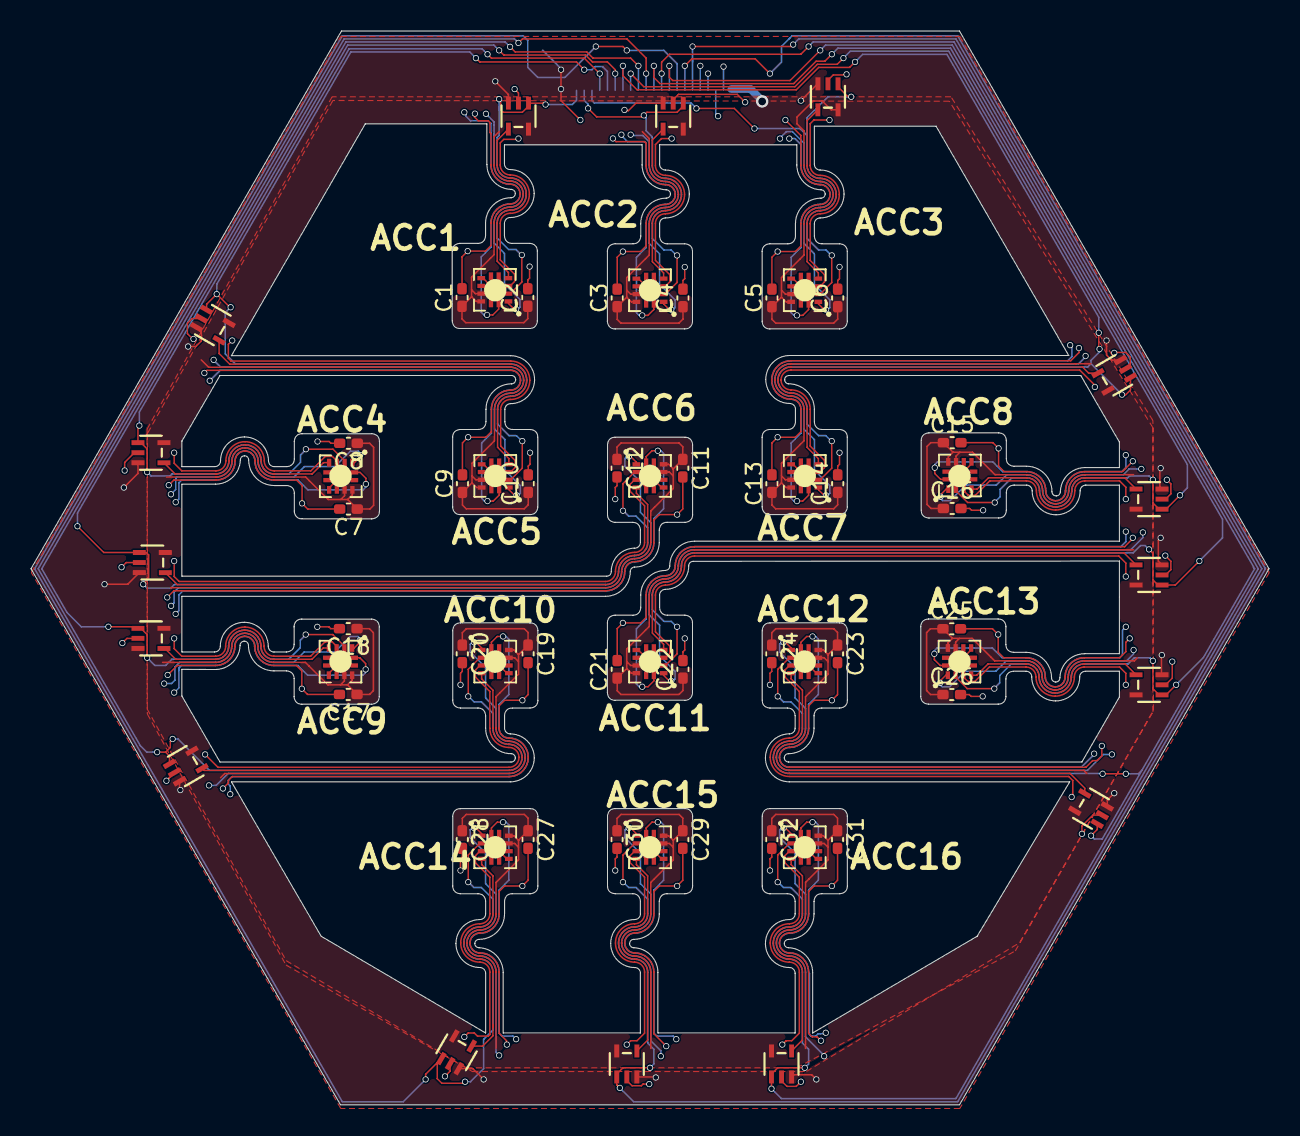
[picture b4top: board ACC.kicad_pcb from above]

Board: 4 copper layers, 80.0 x 69.4 mm, 65 parts (1 on the bottom side), 37 nets.

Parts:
C1, C3, C5, C7, C9, C11, C13, C15, C17, C19, C21, C23, C25, C27, C29, C31: 100n; C_0402_1005Metric_Pad0.74x0.62mm_HandSolder
C2, C4, C6, C8, C10, C12, C14, C16, C18, C20, C22, C24, C26, C28, C30, C32: 1uF; C_0402_1005Metric_Pad0.74x0.62mm_HandSolder
FFC_connector1: AFC01-S22FCA-00
U1, U2, U3, U4, U5, U6, U7, U8, U9, U10, U11, U12, U13, U14, U15, U16: LIS2DH12TR
U17, U18, U19, U20, U21, U22, U23, U24, U25, U26, U27, U28, U29, U30, U31, U32: SN74LVC1G32DCKR

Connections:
GND: C1.2, C2.2, C3.2, C4.2, C5.2, C6.2, C7.2, C8.2, C9.2, C10.2, C11.2, C12.2, C13.2, C14.2, C15.2, C16.2, C17.2, C18.2, C19.2, C20.2, C21.2, C22.2, C23.2, C24.2, C25.2, C26.2, C27.2, C28.2, C29.2, C30.2, C31.2, C32.2, FFC_connector1.22, FFC_connector1.23, FFC_connector1.24, U1.5 (RES), U1.6 (GND), U1.7 (GND), U1.8 (GND), U2.5 (RES), U2.6 (GND), U2.7 (GND), U2.8 (GND), U3.5 (RES), U3.6 (GND), U3.7 (GND), U3.8 (GND), U4.5 (RES), U4.6 (GND), U4.7 (GND), U4.8 (GND), U5.5 (RES), U5.6 (GND), U5.7 (GND), U5.8 (GND), U6.5 (RES), U6.6 (GND), U6.7 (GND), U6.8 (GND), U7.5 (RES), U7.6 (GND), U7.7 (GND), U7.8 (GND), U8.5 (RES), U8.6 (GND), U8.7 (GND), U8.8 (GND), U9.5 (RES), U9.6 (GND), U9.7 (GND), U9.8 (GND), U10.5 (RES), U10.6 (GND), U10.7 (GND), U10.8 (GND), U11.5 (RES), U11.6 (GND), U11.7 (GND), U11.8 (GND), U12.5 (RES), U12.6 (GND), U12.7 (GND), U12.8 (GND), U13.5 (RES), U13.6 (GND), U13.7 (GND), U13.8 (GND), U14.5 (RES), U14.6 (GND), U14.7 (GND), U14.8 (GND), U15.5 (RES), U15.6 (GND), U15.7 (GND), U15.8 (GND), U16.5 (RES), U16.6 (GND), U16.7 (GND), U16.8 (GND), U17.3 (GND), U18.3 (GND), U19.3 (GND), U20.3 (GND), U21.3 (GND), U22.3 (GND), U23.3 (GND), U24.3 (GND), U25.3 (GND), U26.3 (GND), U27.3 (GND), U28.3 (GND), U29.3 (GND), U30.3 (GND), U31.3 (GND), U32.3 (GND)
MISO(SDO): FFC_connector1.2, U1.3 (SDO/SA0), U2.3 (SDO/SA0), U3.3 (SDO/SA0), U4.3 (SDO/SA0), U5.3 (SDO/SA0), U6.3 (SDO/SA0), U7.3 (SDO/SA0), U8.3 (SDO/SA0), U9.3 (SDO/SA0), U10.3 (SDO/SA0), U11.3 (SDO/SA0), U12.3 (SDO/SA0), U13.3 (SDO/SA0), U14.3 (SDO/SA0), U15.3 (SDO/SA0), U16.3 (SDO/SA0)
MOSI(SDI): FFC_connector1.4, U17.2 (B), U18.2 (B), U19.2 (B), U20.2 (B), U21.2 (B), U22.2 (B), U23.2 (B), U24.2 (B), U25.2 (B), U26.2 (B), U27.2 (B), U28.2 (B), U29.2 (B), U30.2 (B), U31.2 (B), U32.2 (B)
unnamed: U1.4 (SDA/SDI/SDO), U17.4 (Y)
unnamed: U10.4 (SDA/SDI/SDO), U26.4 (Y)
unnamed: U11.4 (SDA/SDI/SDO), U27.4 (Y)
unnamed: U12.4 (SDA/SDI/SDO), U28.4 (Y)
unnamed: U13.4 (SDA/SDI/SDO), U29.4 (Y)
unnamed: U14.4 (SDA/SDI/SDO), U30.4 (Y)
unnamed: U15.4 (SDA/SDI/SDO), U31.4 (Y)
unnamed: U16.4 (SDA/SDI/SDO), U32.4 (Y)
unnamed: U2.4 (SDA/SDI/SDO), U18.4 (Y)
unnamed: U3.4 (SDA/SDI/SDO), U19.4 (Y)
unnamed: U4.4 (SDA/SDI/SDO), U20.4 (Y)
unnamed: U5.4 (SDA/SDI/SDO), U21.4 (Y)
unnamed: U6.4 (SDA/SDI/SDO), U22.4 (Y)
unnamed: U7.4 (SDA/SDI/SDO), U23.4 (Y)
unnamed: U8.4 (SDA/SDI/SDO), U24.4 (Y)
unnamed: U9.4 (SDA/SDI/SDO), U25.4 (Y)
Sclk: FFC_connector1.3, U1.1 (SCL/SPC), U2.1 (SCL/SPC), U3.1 (SCL/SPC), U4.1 (SCL/SPC), U5.1 (SCL/SPC), U6.1 (SCL/SPC), U7.1 (SCL/SPC), U8.1 (SCL/SPC), U9.1 (SCL/SPC), U10.1 (SCL/SPC), U11.1 (SCL/SPC), U12.1 (SCL/SPC), U13.1 (SCL/SPC), U14.1 (SCL/SPC), U15.1 (SCL/SPC), U16.1 (SCL/SPC)
VDD: C1.1, C2.1, C3.1, C4.1, C5.1, C6.1, C7.1, C8.1, C9.1, C10.1, C11.1, C12.1, C13.1, C14.1, C15.1, C16.1, C17.1, C18.1, C19.1, C20.1, C21.1, C22.1, C23.1, C24.1, C25.1, C26.1, C27.1, C28.1, C29.1, C30.1, C31.1, C32.1, FFC_connector1.1, U1.9 (VDD), U1.10 (VDD_IO), U2.9 (VDD), U2.10 (VDD_IO), U3.9 (VDD), U3.10 (VDD_IO), U4.9 (VDD), U4.10 (VDD_IO), U5.9 (VDD), U5.10 (VDD_IO), U6.9 (VDD), U6.10 (VDD_IO), U7.9 (VDD), U7.10 (VDD_IO), U8.9 (VDD), U8.10 (VDD_IO), U9.9 (VDD), U9.10 (VDD_IO), U10.9 (VDD), U10.10 (VDD_IO), U11.9 (VDD), U11.10 (VDD_IO), U12.9 (VDD), U12.10 (VDD_IO), U13.9 (VDD), U13.10 (VDD_IO), U14.9 (VDD), U14.10 (VDD_IO), U15.9 (VDD), U15.10 (VDD_IO), U16.9 (VDD), U16.10 (VDD_IO), U17.5 (VCC), U18.5 (VCC), U19.5 (VCC), U20.5 (VCC), U21.5 (VCC), U22.5 (VCC), U23.5 (VCC), U24.5 (VCC), U25.5 (VCC), U26.5 (VCC), U27.5 (VCC), U28.5 (VCC), U29.5 (VCC), U30.5 (VCC), U31.5 (VCC), U32.5 (VCC)
nCS_1: FFC_connector1.21, U1.2 (CS), U17.1 (A)
nCS_2: FFC_connector1.20, U2.2 (CS), U18.1 (A)
nCS_3: FFC_connector1.19, U3.2 (CS), U19.1 (A)
nCS_4: FFC_connector1.18, U4.2 (CS), U20.1 (A)
nCS_5: FFC_connector1.17, U5.2 (CS), U21.1 (A)
nCS_6: FFC_connector1.16, U6.2 (CS), U22.1 (A)
nCS_7: FFC_connector1.15, U7.2 (CS), U23.1 (A)
nCS_8: FFC_connector1.14, U8.2 (CS), U24.1 (A)
nCS_9: FFC_connector1.13, U9.2 (CS), U25.1 (A)
nCS_10: FFC_connector1.12, U10.2 (CS), U26.1 (A)
nCS_11: FFC_connector1.11, U11.2 (CS), U27.1 (A)
nCS_12: FFC_connector1.10, U12.2 (CS), U28.1 (A)
nCS_13: FFC_connector1.9, U13.2 (CS), U29.1 (A)
nCS_14: FFC_connector1.8, U14.2 (CS), U30.1 (A)
nCS_15: FFC_connector1.7, U15.2 (CS), U31.1 (A)
nCS_16: FFC_connector1.6, U16.2 (CS), U32.1 (A)
